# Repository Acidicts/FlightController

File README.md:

# My Simple Flight Controller
Made by following a tutorial by @notaroomba

<div style="display:inline-block">

</div>

## I learnt:
- That you can route sections of a pcb the bring them together to finish
- How to do ground fill in KiCAD
- That texas instruments is a good site to look on

## Features
| Name | Description | Part Name | Usage |
| --- | --- | --- | --- |
| MCU | High Speed MCU | STM32F722RET6 | This is the brains and allows management of all the other components connected to it |
| Barometer | For relative height measuring from launch altitude | BMP580 | This allows altitude tracking for each flight mission |
| IMU | Tracks movement | ICM-45686 | This allows tracking of the flight path and orientation of the craft using the 3 axis gyroscope in it |
| Battery Charger | Manages battery charging for Lithium Batteries | BQ25883RGER | This manages the battery and allows smooth discharge and charging of the battery to prevent damage to the battery and the board |
| High speed clock | Provides high-speed frequency to MCU (~25MHz) | X322525MOB4SI | This provides the main clock signal for the MCU |
| Low speed clock | Provides low-speed frequency to MCU (32.768kHz) | Q13FC13500004 | This provides a stable time base for the MCU |
| Battery Screw Terminal | For connecting battery | XY308-2.54-2P | This allows easy connection of the battery to the board (no soldering today) |
| Two servo pin headers | For connecting the servos | 2.54-1*3P | This allows easy connection of the servos to the board allowing hot swapping servos or cables |

## Getting Started
Click [here](GETTING_STARTED.md)

## BOM
[BOM](./BOM.csv)

[PCB BOM](./PCB_BOM.csv)

[PCB BOM UNSELECTED](./PCB_BOM_UNSELECTED.csv) - Most due to not being in stock or I couldn't find them on lcsc

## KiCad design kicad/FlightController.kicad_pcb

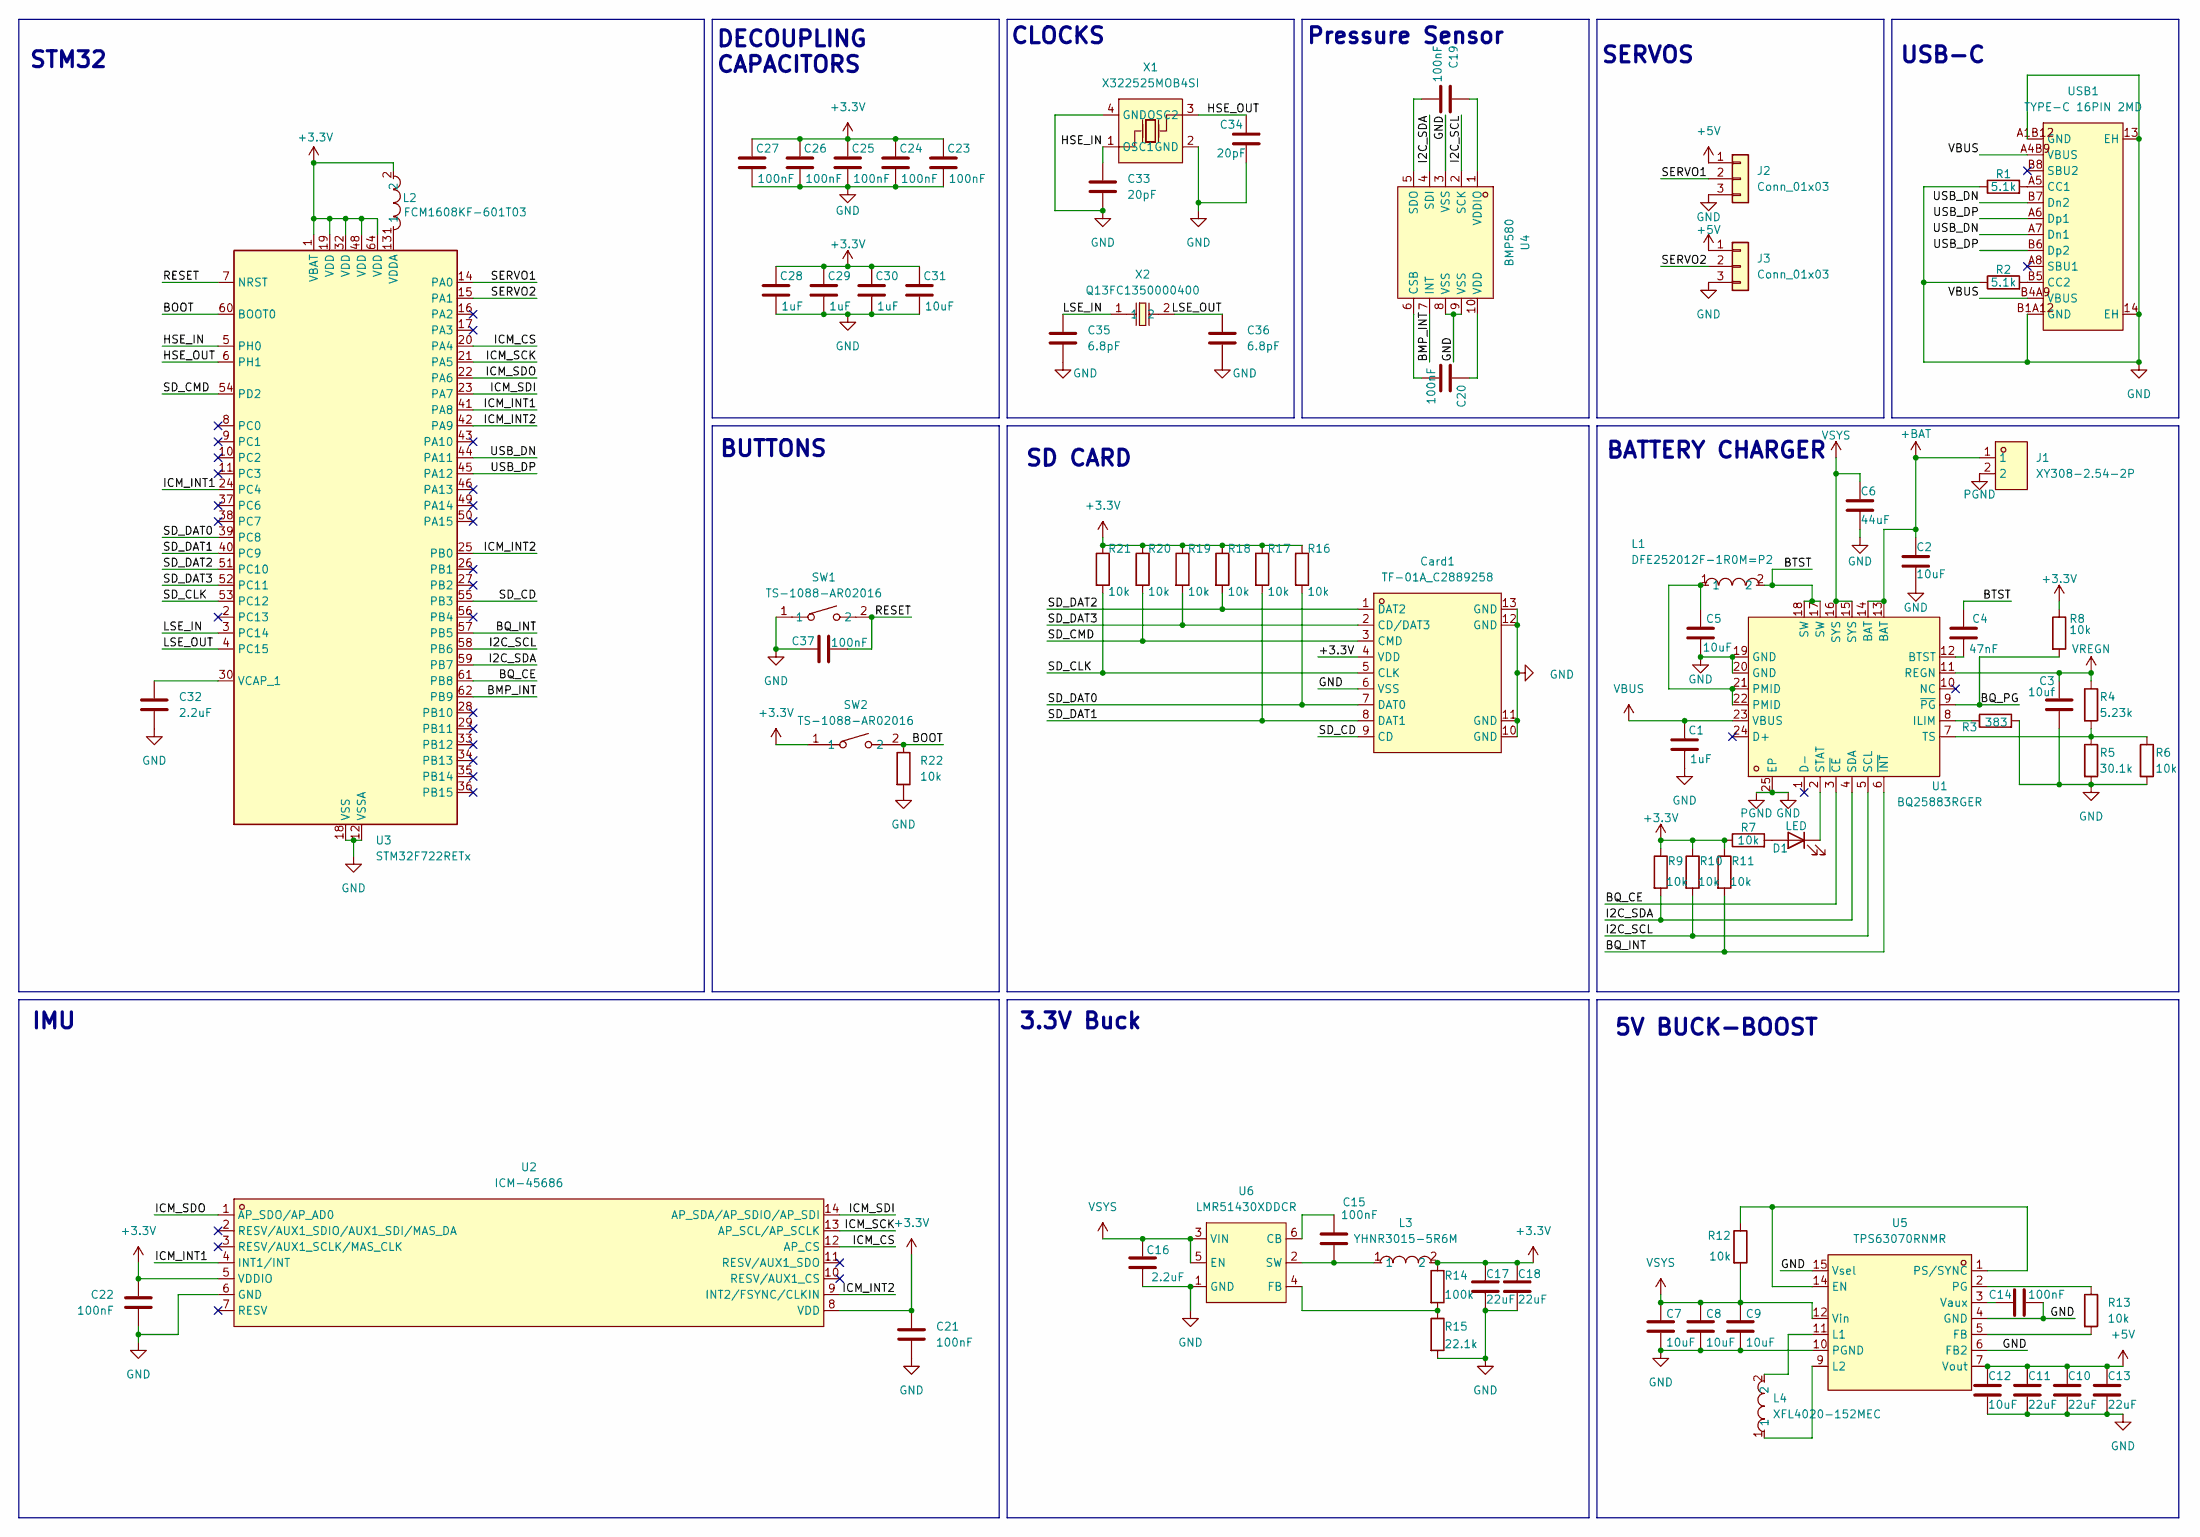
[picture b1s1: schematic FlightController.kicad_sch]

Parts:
C1, C28, C29, C30: 1uF; C_0402_1005Metric
C2, C31: 10uF; C_0603_1608Metric
C3: 10uf; C_0402_1005Metric
C4: 47nF; C_0201_0603Metric
C5, C7, C8, C9, C12: 10uF; C_0402_1005Metric
C6: 44uF; C_0603_1608Metric
C10, C11, C13: 22uF; C_0805_2012Metric
C14, C15: 100nF; C_0402_1005Metric
C16, C32: 2.2uF; C_0402_1005Metric
C17, C18: 22uF; C_0402_1005Metric
C19, C20, C21, C22, C23, C24, C25, C26, C27, C37: 100nF; C_0201_0603Metric
C33, C34: 20pF; C_0201_0603Metric
C35, C36: 6.8pF; C_0201_0603Metric
Card1: TF-01A_C2889258; TF-SMD_TF-02; MPN TF-01A; LCSC Part C2889258
D1: LED; LED_0402_1005Metric
J1: XY308-2.54-2P; CONN-TH_XY308-2.54-2P; MPN XY308-2.54-2P; LCSC Part C557685
J2, J3: Conn_01x03; PinHeader_1x03_P2.54mm_Vertical
L1: DFE252012F-1R0M=P2; L2520; MPN DFE252012F-1R0M=P2; LCSC Part C435392
L2: FCM1608KF-601T03; L0603; MPN FCM1608KF-601T03; LCSC Part C141723
L3: YHNR3015-5R6M; IND-SMD_L3.0-W3.0; MPN YHNR3015-5R6M; LCSC Part C18236327
L4: XFL4020-152MEC; IND-SMD_L4.0-W4.0-A; MPN XFL4020-152MEC; LCSC Part C3033018
R1, R2: 5.1k; R_0201_0603Metric
R3: 383; R_0201_0603Metric
R4: 5.23k; R_0201_0603Metric
R5: 30.1k; R_0201_0603Metric
R6, R7, R8, R9, R10, R11, R12, R13, R16, R17, R18, R19, R20, R21, R22: 10k; R_0201_0603Metric
R14: 100k; R_0402_1005Metric
R15: 22.1k; R_0201_0603Metric
SW1, SW2: TS-1088-AR02016; SW-SMD_L3.9-W3.0-P4.45; MPN TS-1088-AR02016; LCSC Part C720477
U1: BQ25883RGER; VFQFPN-24_L4.0-W4.0-P0.50-BL-EP2.8; MPN BQ25883RGER; LCSC Part C544362
U2: ICM-45686; LGA-14_L3.0-W2.5-P0.50-TL; MPN ICM-45686; LCSC Part C22459454
U3: STM32F722RETx; LQFP-64_10x10mm_P0.5mm
U4: BMP580; LGA-10_L2.0-W2.0-P0.50-TL_BMP580; MPN BMP580; LCSC Part C22391138
U5: TPS63070RNMR; VQFN-15_L3.0-W2.5-P0.50-BL; MPN TPS63070RNMR; LCSC Part C109322
U6: LMR51430XDDCR; SOT-23-6_L2.9-W1.6-P0.95-LS2.8-BL; MPN LMR51430XDDCR; LCSC Part C5185863
USB1: TYPE-C 16PIN 2MD; USB-C-SMD_TYPE-C-16PIN-2MD-073; MPN TYPE-C 16PIN 2MD(073); LCSC Part C2765186
X1: X322525MOB4SI; CRYSTAL-SMD_4P-L3.2-W2.5-BL; MPN X322525MOB4SI; LCSC Part C9006
X2: Q13FC1350000400; FC-135R_L3.2-W1.5; MPN Q13FC13500004; LCSC Part C32346

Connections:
+3.3V: C17.1, C18.1, C21.1, C22.1, C23.1, C24.1, C25.1, C26.1, C27.1, C28.1, C29.1, C30.1, C31.1, Card1.4 (VDD), L2.2, L3.2, R7.1, R8.1, R9.1, R10.1, R11.1, R14.1, R16.1, R17.1, R18.1, R19.1, R20.1, R21.1, SW2.1, U2.5 (VDDIO), U2.8 (VDD), U3.1 (VBAT), U3.19 (VDD), U3.32 (VDD), U3.48 (VDD), U3.64 (VDD)
+5V: C10.1, C11.1, C12.1, C13.1, J2.1, J3.1, U5.7 (Vout)
+BAT: C2.1, J1.1, U1.13 (BAT), U1.14 (BAT)
/BMP_INT: U3.62 (PB9), U4.7 (INT)
/BOOT: R22.1, SW2.2, U3.60 (BOOT0)
/BQ_CE: U1.3 (~CE), U3.61 (PB8)
/BQ_INT: R11.2, U1.6 (~INT), U3.57 (PB5)
/BQ_PG: R8.2, U1.9 (~PG)
/BTST: C4.1, L1.2, U1.17 (SW), U1.18 (SW)
/HSE_IN: C33.1, U3.5 (PH0), X1.1 (OSC1)
/HSE_OUT: C34.1, U3.6 (PH1), X1.3 (OSC2)
/I2C_SCL: R10.2, U1.5 (SCL), U3.58 (PB6), U4.2 (SCK)
/I2C_SDA: R9.2, U1.4 (SDA), U3.59 (PB7), U4.4 (SDI)
/ICM_CS: U2.12 (AP_CS), U3.20 (PA4)
/ICM_INT1: U2.4 (INT1/INT), U3.24 (PC4), U3.41 (PA8)
/ICM_INT2: U2.9 (INT2/FSYNC/CLKIN), U3.25 (PB0), U3.42 (PA9)
/ICM_SCK: U2.13 (AP_SCL/AP_SCLK), U3.21 (PA5)
/ICM_SDI: U2.14 (AP_SDA/AP_SDIO/AP_SDI), U3.23 (PA7)
/ICM_SDO: U2.1 (AP_SDO/AP_AD0), U3.22 (PA6)
/LSE_IN: C35.1, U3.3 (PC14), X2.1
/LSE_OUT: C36.1, U3.4 (PC15), X2.2
/RESET: C37.2, SW1.2, U3.7 (NRST)
/SD_CD: Card1.9 (CD), U3.55 (PB3)
/SD_CLK: Card1.5 (CLK), R21.2, U3.53 (PC12)
/SD_CMD: Card1.3 (CMD), R20.2, U3.54 (PD2)
/SD_DAT0: Card1.7 (DAT0), R16.2, U3.39 (PC8)
/SD_DAT1: Card1.8 (DAT1), R17.2, U3.40 (PC9)
/SD_DAT2: Card1.1 (DAT2), R18.2, U3.51 (PC10)
/SD_DAT3: Card1.2 (CD/DAT3), R19.2, U3.52 (PC11)
/SERVO1: J2.2, U3.14 (PA0)
/SERVO2: J3.2, U3.15 (PA1)
/USB_DN: U3.44 (PA11), USB1.A7 (Dn1), USB1.B7 (Dn2)
/USB_DP: U3.45 (PA12), USB1.A6 (Dp1), USB1.B6 (Dp2)
GND: C1.2, C2.2, C3.2, C5.2, C6.2, C7.2, C8.2, C9.2, C10.2, C11.2, C12.2, C13.2, C14.2, C16.2, C17.2, C18.2, C21.2, C22.2, C23.2, C24.2, C25.2, C26.2, C27.2, C28.2, C29.2, C30.2, C31.2, C32.2, C33.2, C34.2, C35.2, C36.2, C37.1, Card1.6 (VSS), Card1.10 (GND), Card1.11 (GND), Card1.12 (GND), Card1.13 (GND), J1.2, J2.3, J3.3, R1.1, R2.1, R3.2, R5.2, R6.2, R15.2, R22.2, SW1.1, U1.19 (GND), U1.20 (GND), U1.25 (EP), U2.6 (GND), U3.12 (VSSA), U3.18 (VSS), U3.31 (VSS), U3.47 (VSS), U3.63 (VSS), U4.3 (VSS), U4.8 (VSS), U4.9 (VSS), U5.4 (GND), U5.6 (FB2), U5.10 (PGND), U5.15 (Vsel), U6.1 (GND), USB1.13 (EH), USB1.14 (EH), USB1.A1B12 (GND), USB1.B1A12 (GND), X1.2 (GND), X1.4 (GND)
unnamed: C5.1, L1.1, U1.21 (PMID), U1.22 (PMID)
unnamed: D1.2 (A), R7.2
unnamed: D1.1 (K), U1.2 (STAT)
unnamed: C4.2, U1.12 (BTST)
unnamed: R3.1, U1.8 (ILIM)
unnamed: R4.2, R5.1, R6.1, U1.7 (TS)
unnamed: C32.1, U3.30 (VCAP_1)
unnamed: L2.1, U3.13 (VDDA)
unnamed: C20.2, U4.6 (CSB)
unnamed: C19.2, U4.5 (SDO)
unnamed: C20.1, U4.10 (VDD)
unnamed: C19.1, U4.1 (VDDIO)
unnamed: R12.1, U5.1 (PS/SYNC), U5.14 (EN)
unnamed: R13.2, U5.5 (FB)
unnamed: L4.2, U5.11 (L1)
unnamed: L4.1, U5.9 (L2)
unnamed: R13.1, U5.2 (PG)
unnamed: C14.1, U5.3 (Vaux)
unnamed: C15.1, U6.6 (CB)
unnamed: R14.2, R15.1, U6.4 (FB)
unnamed: C15.2, L3.1, U6.2 (SW)
unnamed: R1.2, USB1.A5 (CC1)
unnamed: R2.2, USB1.B5 (CC2)
VBUS: C1.1, U1.23 (VBUS), USB1.A4B9 (VBUS), USB1.B4A9 (VBUS)
VREGN: C3.1, R4.1, U1.11 (REGN)
VSYS: C6.1, C7.1, C8.1, C9.1, C16.1, R12.2, U1.15 (SYS), U1.16 (SYS), U5.12 (Vin), U6.3 (VIN), U6.5 (EN)

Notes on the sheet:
BUTTONS
SERVOS
IMU
CLOCKS
SD CARD
5V BUCK-BOOST
DECOUPLING CAPACITORS
STM32
BATTERY CHARGER
Pressure Sensor
USB-C
3.3V Buck

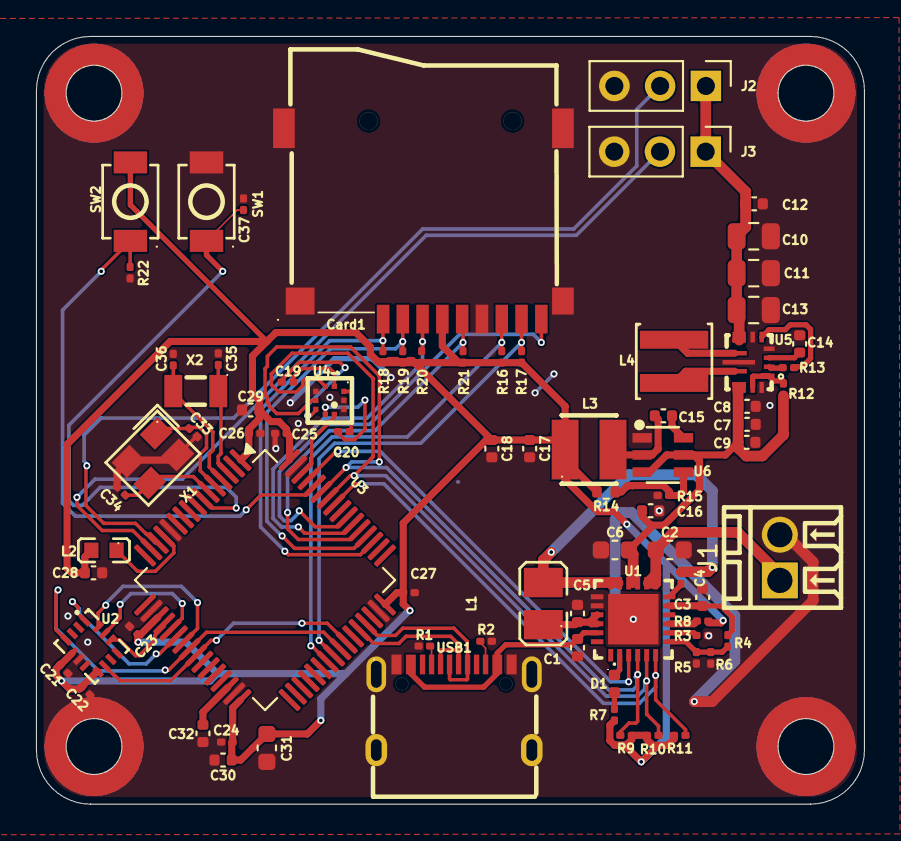
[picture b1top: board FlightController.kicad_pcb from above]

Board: 2 copper layers, 46.0 x 42.6 mm, 79 parts (0 on the bottom side), 60 nets.

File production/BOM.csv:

Designator,Footprint,Quantity,Value,LCSC Part #
"C1, C28, C29, C30",0402,4,1uF,
"C10, C11, C13",0805,3,22uF,
"C12, C3, C5, C7, C8, C9",0402,6,10uF,
"C14, C15",0402,2,100nF,
"C16, C32",0402,2,2.2uF,
"C17, C18",0402,2,22uF,
"C19, C20, C21, C22, C23, C24, C25, C26, C27, C37",0201,10,100nF,
"C2, C31",0603,2,10uF,
"C33, C34",0201,2,20pF,
"C35, C36",0201,2,6.8pF,
C4,0201,1,47nF,
C6,0603,1,44uF,
CARD1,TF-SMD_TF-02,1,TF-01A_C2889258,C2889258
D1,0402,1,LED,
J1,CONN-TH_XY308-2.54-2P,1,XY308-2.54-2P,C557685
"J2, J3",PinHeader_1x03_P2.54mm_Vertical,2,Conn_01x03,
L1,L2520,1,DFE252012F-1R0M=P2,C435392
L2,L0603,1,FCM1608KF-601T03,C141723
L3,IND-SMD_L3.0-W3.0,1,YHNR3015-5R6M,C18236327
L4,IND-SMD_L4.0-W4.0-A,1,XFL4020-152MEC,C3033018
"R1, R2",0201,2,5.1k,
"R10, R11, R12, R13, R16, R17, R18, R19, R20, R21, R22, R6, R7, R8, R9",0201,15,10k,
R14,0402,1,100k,
R15,0201,1,22.1k,
R3,0201,1,383,
R4,0201,1,5.23k,
R5,0201,1,30.1k,
"SW1, SW2",SW-SMD_L3.9-W3.0-P4.45,2,TS-1088-AR02016,C720477
U1,VFQFPN-24_L4.0-W4.0-P0.50-BL-EP2.8,1,BQ25883RGER,C544362
U2,LGA-14_L3.0-W2.5-P0.50-TL,1,ICM-45686,C22459454
U3,LQFP-64_10x10mm_P0.5mm,1,STM32F722RETx,
U4,LGA-10_L2.0-W2.0-P0.50-TL_BMP580,1,BMP580,C22391138
U5,VQFN-15_L3.0-W2.5-P0.50-BL,1,TPS63070RNMR,C109322
U6,SOT-23-6_L2.9-W1.6-P0.95-LS2.8-BL,1,LMR51430XDDCR,C5185863
USB1,USB-C-SMD_TYPE-C-16PIN-2MD-073,1,TYPE-C 16PIN 2MD,C2765186
X1,CRYSTAL-SMD_4P-L3.2-W2.5-BL,1,X322525MOB4SI,C9006
X2,FC-135R_L3.2-W1.5,1,Q13FC1350000400,C32346

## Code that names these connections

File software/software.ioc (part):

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Mcu.Name=STM32F722R(C-E)Tx
Mcu.Package=LQFP64
Mcu.UserName=STM32F722RETx
PA0-WKUP.Signal=S_TIM2_CH1_ETR
PA1.Signal=S_TIM2_CH2
PA11.Mode=Host_Only
PA11.Signal=USB_OTG_FS_DM
PA12.Mode=Host_Only
PA12.Signal=USB_OTG_FS_DP
PA4.Mode=NSS_Signal_Hard_Output
PA4.Signal=SPI1_NSS
PA5.Mode=Full_Duplex_Master
PA5.Signal=SPI1_SCK
PA6.Mode=Full_Duplex_Master
PA6.Signal=SPI1_MISO
PA7.Mode=Full_Duplex_Master
PA7.Signal=SPI1_MOSI
PB0.GPIOParameters=GPIO_Label
PB0.GPIO_Label=ICM_INT2
PB0.Signal=GPXTI0
PB3.GPIOParameters=GPIO_Label
PB3.GPIO_Label=SD_CS
PB3.Signal=GPIO_Input
PB5.GPIOParameters=GPIO_Label
PB5.GPIO_Label=BQ_INT
PB5.Signal=GPXTI5
PB6.Mode=I2C
PB6.Signal=I2C1_SCL
PB7.Mode=I2C
PB7.Signal=I2C1_SDA
PB8.GPIOParameters=GPIO_Label
PB8.GPIO_Label=BQ_CE
PB8.Signal=GPIO_Output
PB9.GPIOParameters=GPIO_Label
PB9.GPIO_Label=BMP_INT
PB9.Signal=GPXTI9
PC10.Mode=SD_4_bits_Wide_bus
PC10.Signal=SDMMC1_D2
PC11.Mode=SD_4_bits_Wide_bus
PC11.Signal=SDMMC1_D3
PC12.Mode=SD_4_bits_Wide_bus
PC12.Signal=SDMMC1_CK
PC14-OSC32_IN.Mode=LSE-External-Oscillator
PC14-OSC32_IN.Signal=RCC_OSC32_IN
PC15-OSC32_OUT.Mode=LSE-External-Oscillator
PC15-OSC32_OUT.Signal=RCC_OSC32_OUT
PC4.GPIOParameters=GPIO_Label
PC4.GPIO_Label=ICM_INT1
PC4.Signal=GPXTI4
PC8.Mode=SD_4_bits_Wide_bus
PC8.Signal=SDMMC1_D0
PC9.Mode=SD_4_bits_Wide_bus
PC9.Signal=SDMMC1_D1
PD2.Mode=SD_4_bits_Wide_bus
PD2.Signal=SDMMC1_CMD
PH0-OSC_IN.Mode=HSE-External-Oscillator
PH0-OSC_IN.Signal=RCC_OSC_IN
PH1-OSC_OUT.Mode=HSE-External-Oscillator
PH1-OSC_OUT.Signal=RCC_OSC_OUT
RCC.HSE_VALUE=25000000
board=custom
